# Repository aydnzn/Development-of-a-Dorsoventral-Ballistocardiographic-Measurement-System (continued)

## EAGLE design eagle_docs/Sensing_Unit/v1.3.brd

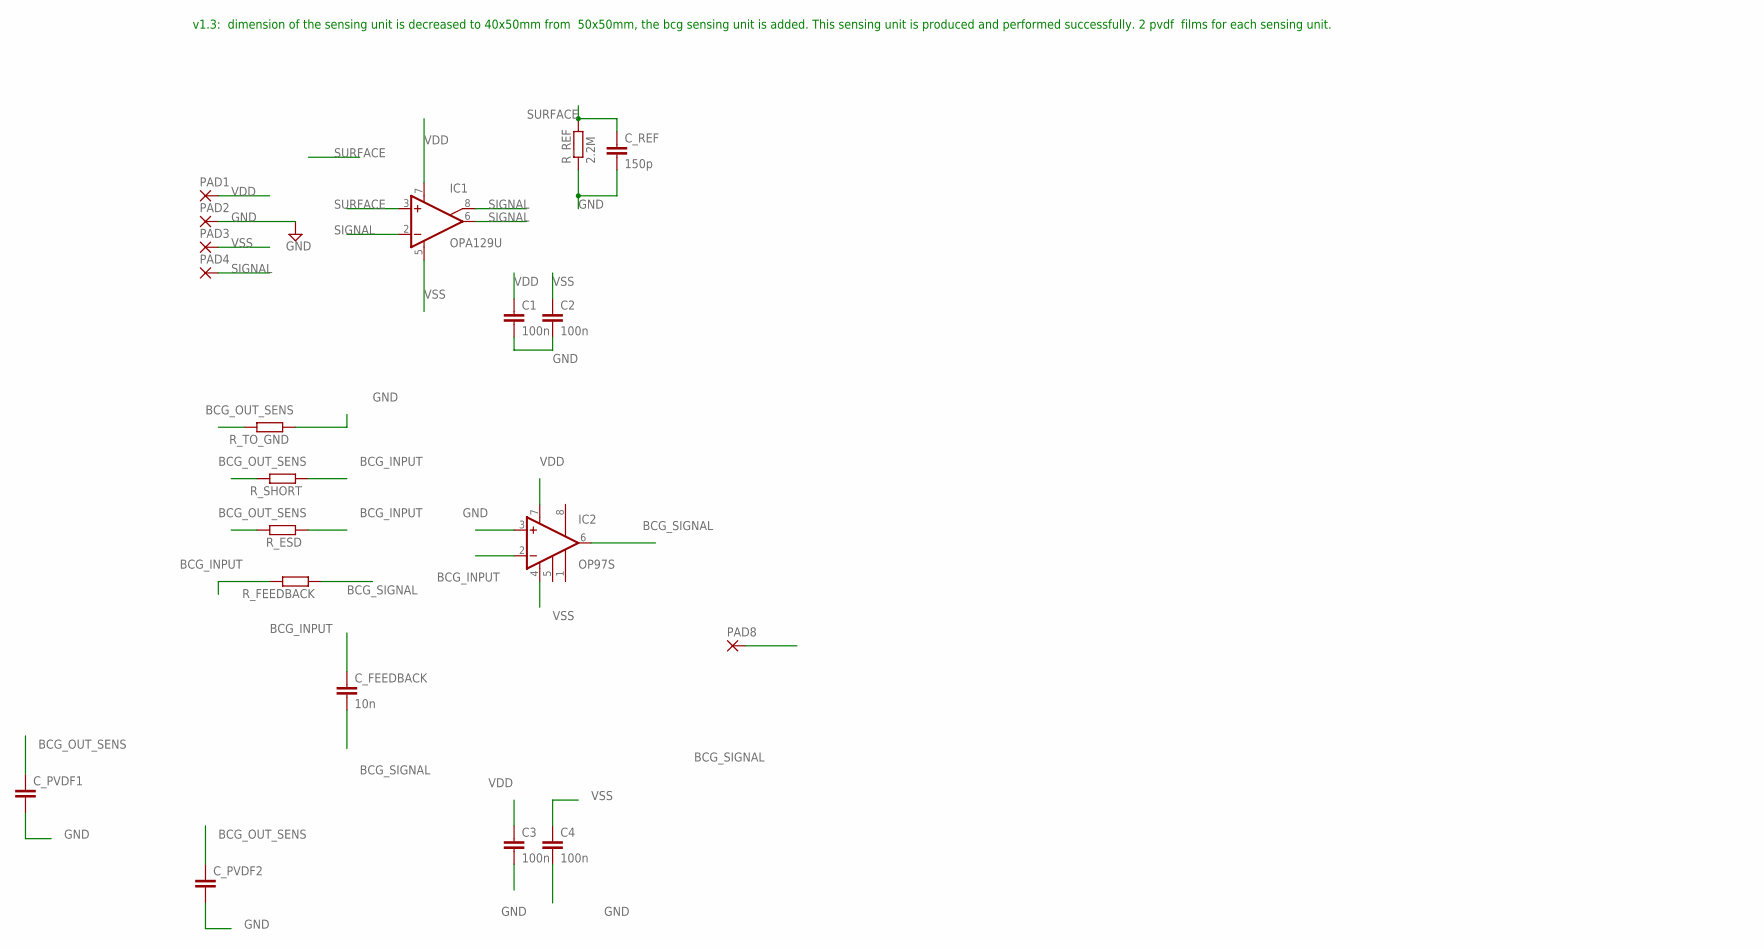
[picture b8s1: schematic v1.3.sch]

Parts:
C1, C2, C3, C4: 100n; C0805
C_FEEDBACK: 10n; C0805
C_PVDF1, C_PVDF2: C-EUC0805; C0805
C_REF: 150p; C0805
IC1: OPA129U; SO08
IC2: OP97S; SO08
PAD1, PAD2, PAD3, PAD4, PAD8: SMD5; SMD2,54-5,08
R_ESD: 1M; M0805
R_FEEDBACK: 100M; M0805
R_REF: 2.2M; M0805
R_SHORT: 1M; M0805
R_TO_GND: 1M; M0805

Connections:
BCG_INPUT: C_FEEDBACK.1, IC2.2 (-IN), R_ESD.1, R_FEEDBACK.2, R_SHORT.1
BCG_OUT_SENS: C_PVDF1.1, C_PVDF2.1, R_ESD.2, R_SHORT.2, R_TO_GND.2
BCG_SIGNAL: C_FEEDBACK.2, IC2.6 (OUT), PAD8.1, R_FEEDBACK.1
GND: C1.2, C2.2, C3.2, C4.2, C_PVDF1.2, C_PVDF2.2, C_REF.2, IC2.3 (+IN), PAD2.1, R_REF.1, R_TO_GND.1
SIGNAL: IC1.2 (-IN), IC1.6 (OUT), IC1.8 (SUBS), PAD4.1
SURFACE: C_REF.1, IC1.3 (+IN), R_REF.2
VDD: C1.1, C3.1, IC1.7 (V+), IC2.7 (V+), PAD1.1
VSS: C2.1, C4.1, IC1.5 (V-), IC2.4 (V-), PAD3.1

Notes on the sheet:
v1.3: dimension of the sensing unit is decreased to 40x50mm from 50x50mm, the bcg sensing unit is added. This sensing unit is produced and performed successfully. 2 pvdf films for each sensing unit.

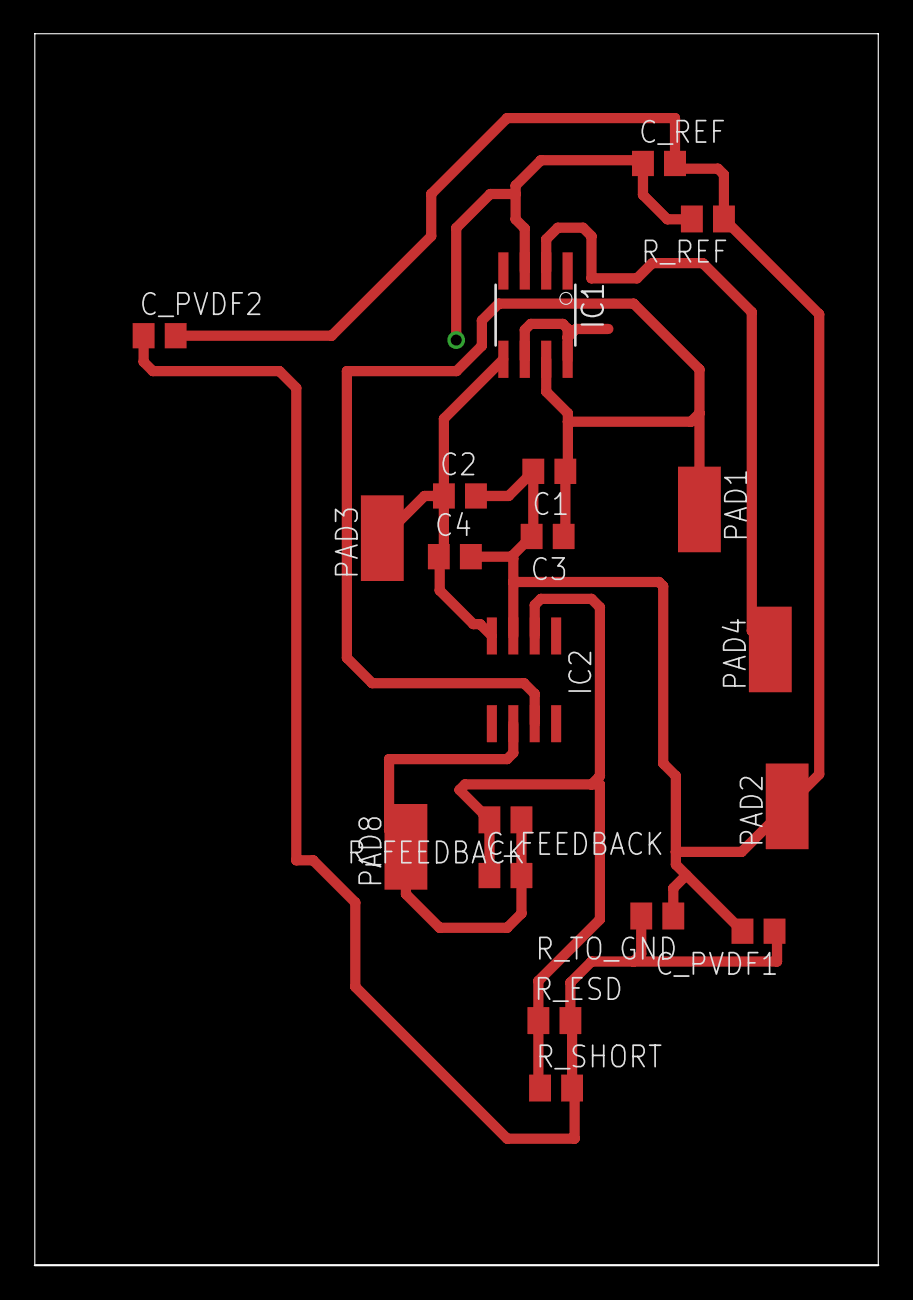
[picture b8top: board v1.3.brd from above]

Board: 2 copper layers, 50.0 x 73.0 mm, 20 parts (0 on the bottom side), 8 nets.

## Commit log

2023-07-21 Create LICENSE
